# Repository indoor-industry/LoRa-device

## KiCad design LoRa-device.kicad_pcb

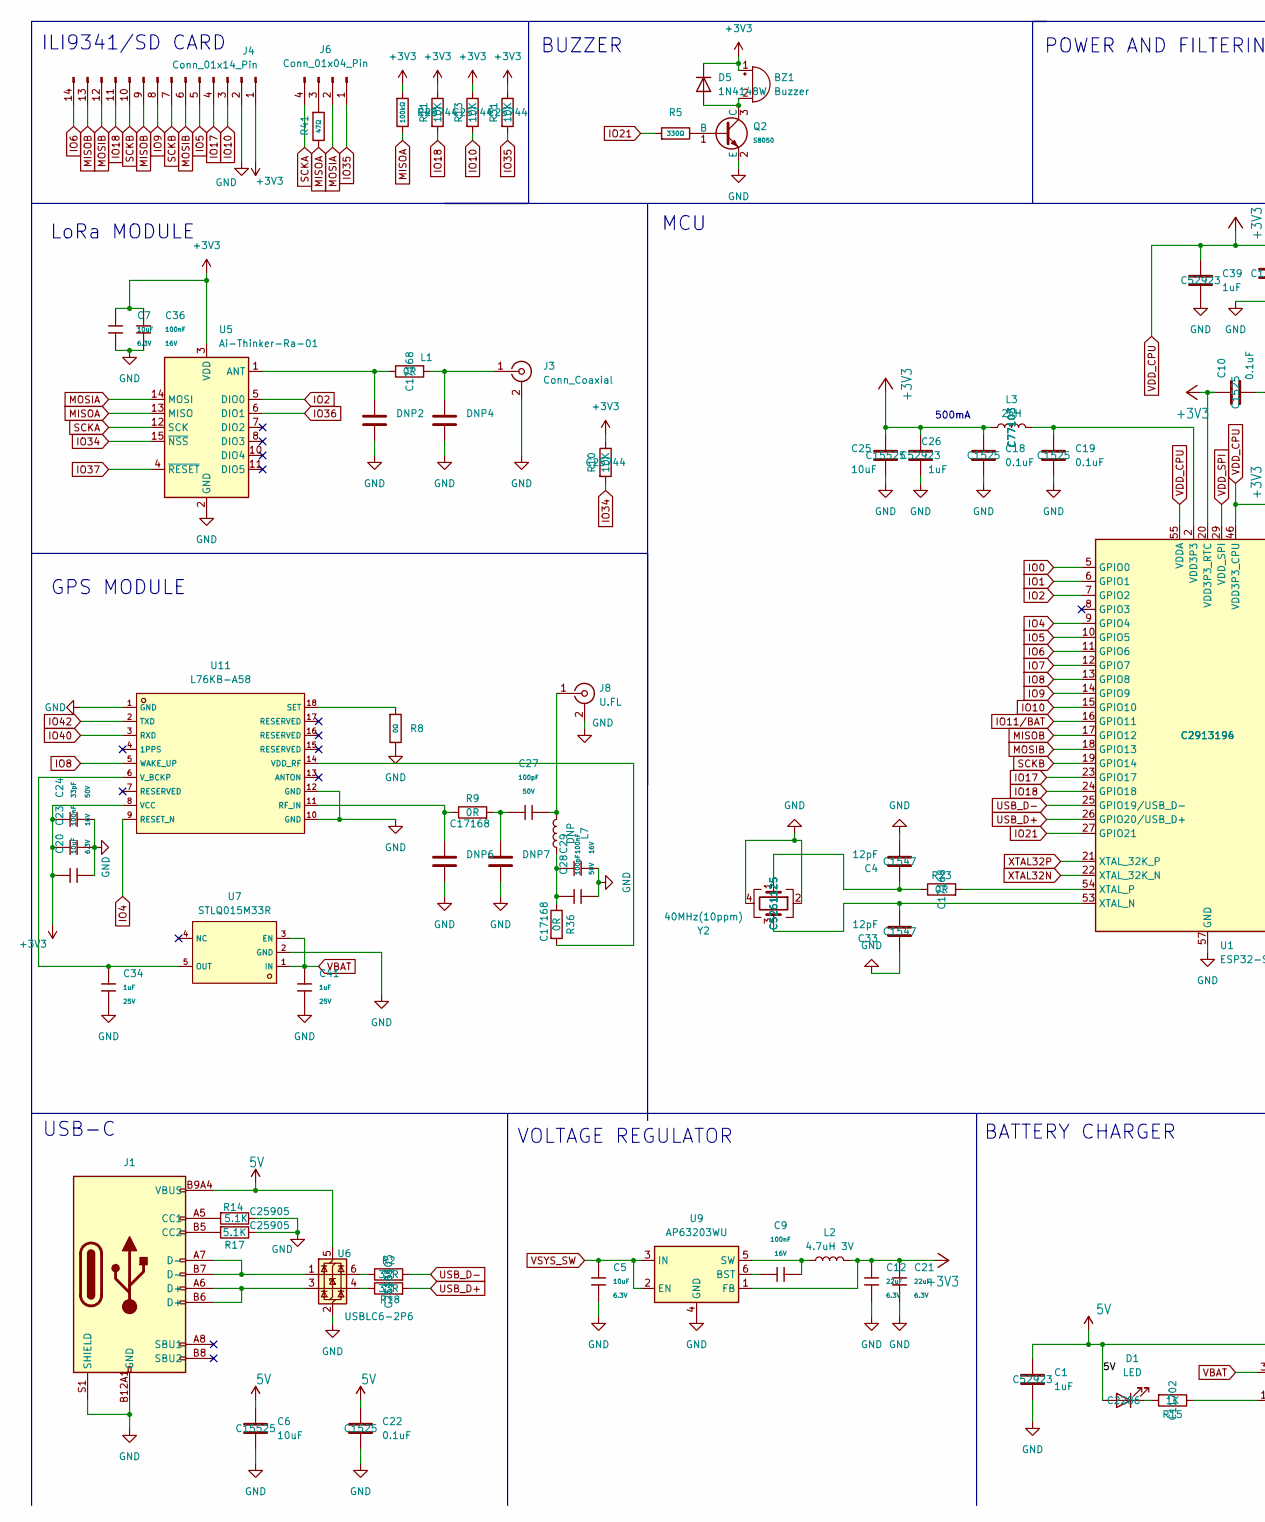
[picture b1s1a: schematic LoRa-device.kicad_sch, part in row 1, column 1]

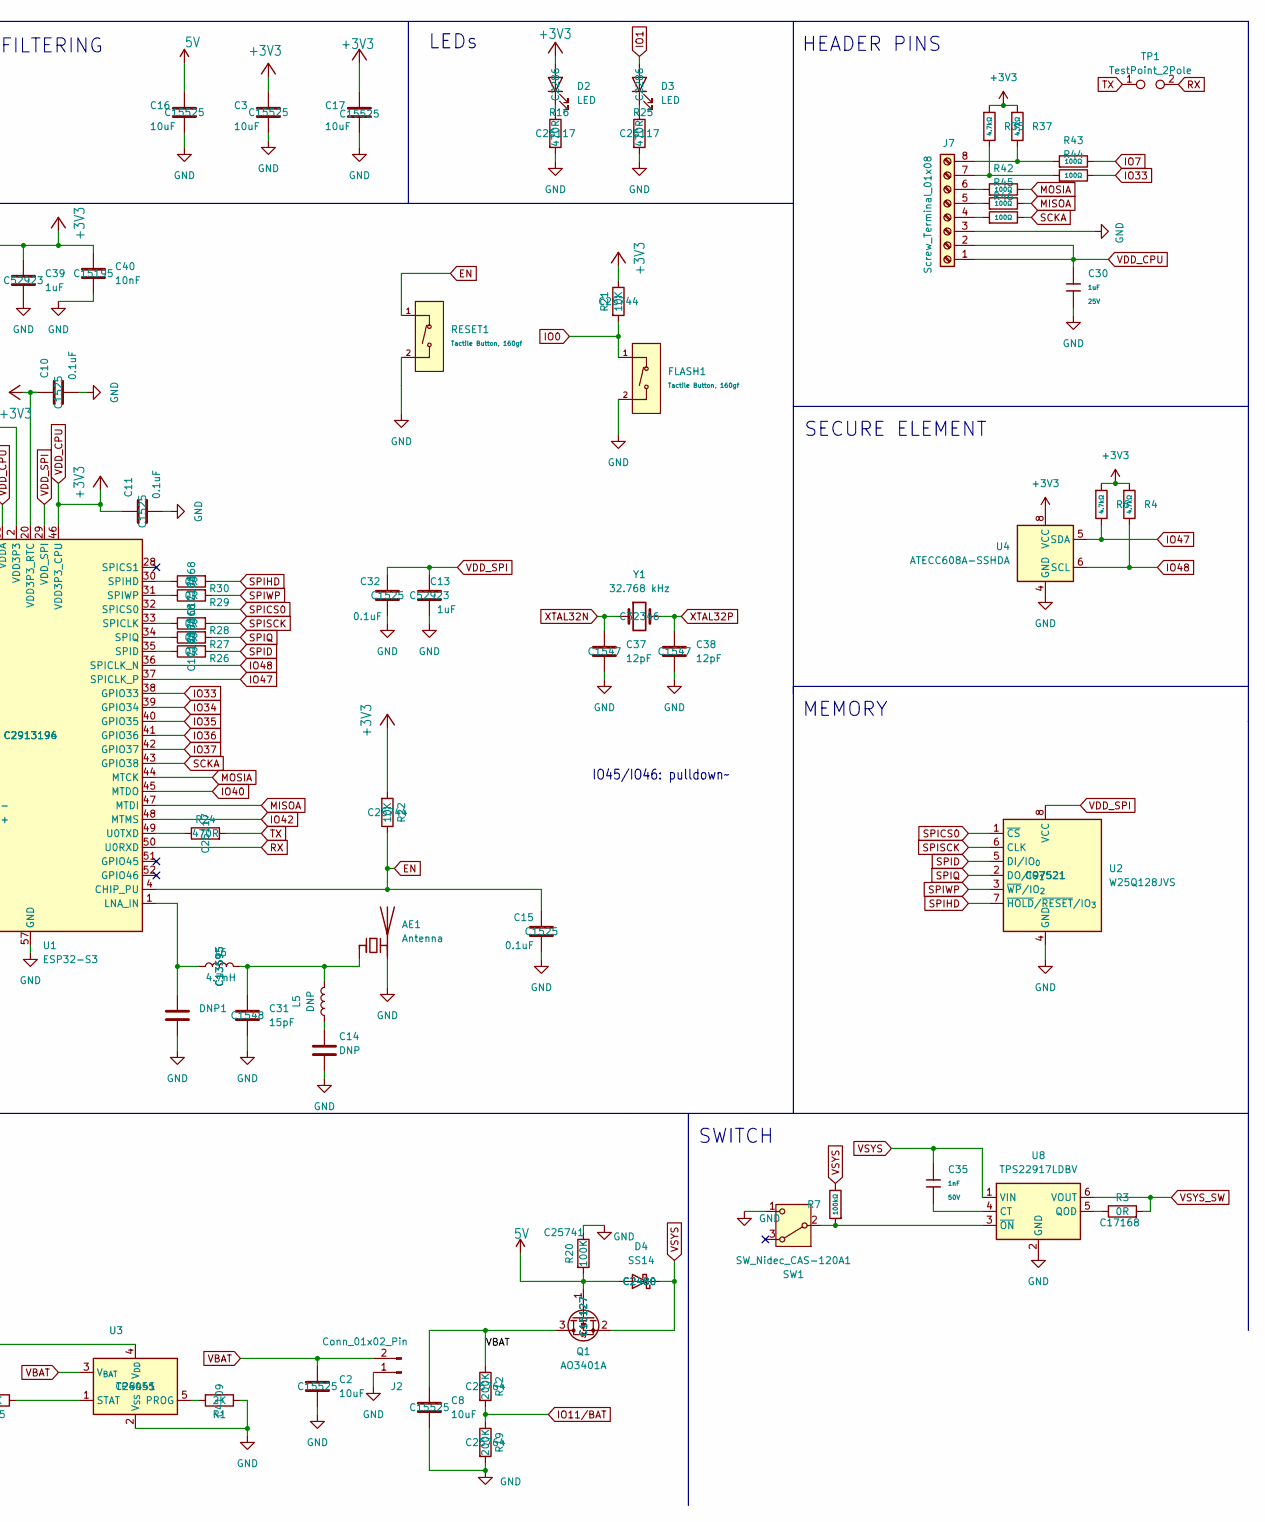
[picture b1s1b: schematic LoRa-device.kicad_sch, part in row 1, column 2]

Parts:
AE1: Antenna; Texas_SWRA117D_2.4GHz_Left
BZ1: Buzzer; MagneticBuzzer_CUI_CMT-8504-100-SMT; MNF PART NUMBER C7437070; LCSC C7437070
C1, C13, C26, C39: 1uF; C_0402_1005Metric; MNF PART NUMBER C52923; LCSC C52923
C2, C3, C6, C8, C16, C17, C25: 10uF; C_0402_1005Metric; MNF PART NUMBER C15525; LCSC C15525
C4, C33, C37, C38: 12pF; C_0402_1005Metric; MNF PART NUMBER C1547; LCSC C1547
C5, C7, C20: 10uF; C_0402; Voltage Rated 6.3V; Tolerance ±20%; Part CL05A106MQ5NUNC; LCSC C15525
C9, C23, C29, C36: 100nF; C_0402; Voltage Rated 16V; Tolerance ±10%; Part CL05B104KO5NNNC; LCSC C1525
C10, C11, C15, C18, C19, C22, C32: 0.1uF; C_0402_1005Metric; MNF PART NUMBER C1525; LCSC C1525
C12, C21: 22uF; C_0603; Voltage Rated 6.3V; Tolerance ±20%; Part CL10A226MQ8NRNC; LCSC C59461
C14: DNP; C_0402_1005Metric
C24: 33pF; C_0402; Voltage Rated 50V; Tolerance ±5%; Part 0402CG330J500NT; LCSC C1562
C27, C28: 100pF; C_0402; Voltage Rated 50V; Tolerance ±5%; Part 0402CG101J500NT; LCSC C1546
C30, C34, C41: 1uF; C_0402; Voltage Rated 25V; Tolerance ±10%; Part CL05A105KA5NQNC; LCSC C52923
C31: 15pF; C_0402_1005Metric; MNF PART NUMBER C1548; LCSC C1548
C35: 1nF; C_0402; Voltage Rated 50V; Tolerance ±10%; Part 0402B102K500NT; LCSC C1523
C40: 10nF; C_0402_1005Metric; MNF PART NUMBER C15195; LCSC C15195
D1, D2, D3: LED; LED_0603_1608Metric; MNF PART NUMBER C2286; LCSC C2286
D4: SS14; LED_0603_1608Metric; MNF PART NUMBER C2480; LCSC C2480
D5: 1N4148W; LED_0603_1608Metric
DNP1, DNP2, DNP4, DNP6, DNP7: C_0402_1005Metric
FLASH1: Tactile Button, 160gf; SW_TS-1088-AR02016; Voltage Rating (Dc) 12V; Part TS-1088-AR02016; LCSC C720477
J1: Connector, USB-TYPE-C-16P; TYPE-C-SMD_HX-TYPE-C-16PIN; LCSC C2927039
J2: Conn_01x02_Pin; PinHeader_1x02_P2.54mm_Vertical
J3: Conn_Coaxial; SMA_Molex_73251-1153_EdgeMount_Horizontal
J4: Conn_01x14_Pin; PinSocket_1x14_P2.54mm_Vertical
J6: Conn_01x04_Pin; PinSocket_1x04_P2.54mm_Vertical
J7: Screw_Terminal_01x08; PhoenixContact_MC_1,5_8-G-3.81_1x08_P3.81mm_Horizontal
J8: U.FL; IPEX-SMD_BWIPX-1-001E; LCSC C5137195
L1: 0R; R_0402_1005Metric; MNF PART NUMBER C17168; LCSC C17168
L2: 4.7uH 3V; L_Sunlord_MWSA0402S; MNF PART NUMBER APH0420T4R7M; LCSC C5349668
L3: 2nH; L_0402_1005Metric; MNF PART NUMBER C77103; LCSC C77103
L5, L7: DNP; L_0402_1005Metric
L6: 4.7nH; L_0402_1005Metric; MNF PART NUMBER C13595; LCSC C13595
Q1: AO3401A; SOT-23; MNF PART NUMBER C15127; LCSC C15127
Q2: S8050; Q_SOT-23; Part S8050; LCSC C364312
R1: 2K; R_0402_1005Metric; MNF PART NUMBER C4109; LCSC C4109
R2, R18: 33R; R_0402_1005Metric; MNF PART NUMBER C25105; LCSC C25105
R3, R9, R23, R26, R27, R28, R29, R30, R36: 0R; R_0402_1005Metric; MNF PART NUMBER C17168; LCSC C17168
R4, R6, R35, R37: 4.7kΩ; R_0402; Overload Voltage (Max) 50V; Tolerance ±1%; Part 0402WGF4701TCE; LCSC C25900
R5: 330Ω; R_0402_1005Metric; Overload Voltage (Max) 50V; Tolerance ±1%; Part 0402WGF3300TCE; LCSC C25104
R7: 100kΩ; R_0402_1005Metric; Overload Voltage (Max) 50V; Tolerance ±1%; Part 0402WGF1003TCE; LCSC C25741
R8: 0Ω; R_0402_1005Metric; Overload Voltage (Max) 50V; Tolerance ±1%; Part 0402WGF0000TCE; LCSC C17168
R10, R11, R13, R21, R22, R31: 10K; R_0402_1005Metric; MNF PART NUMBER C25744; LCSC C25744
R12, R19: 200K; R_0402_1005Metric; MNF PART NUMBER C25764; LCSC C25764
R14, R17: 5.1K; R_0402_1005Metric; MNF PART NUMBER C25905; LCSC C25905
R15: 1K; R_0402_1005Metric; MNF PART NUMBER C11702; LCSC C11702
R16, R24, R25: 470R; R_0402_1005Metric; MNF PART NUMBER C25117; LCSC C25117
R20: 100K; R_0402_1005Metric; MNF PART NUMBER C25741; LCSC C25741
R40: 100kΩ; R_0402; Overload Voltage (Max) 50V; Tolerance ±1%; Part 0402WGF1003TCE; LCSC C25741
R41: 47Ω; R_0402; Overload Voltage (Max) 50V; Tolerance ±1%; Part 0402WGF470JTCE; LCSC C25118
R42, R43, R44, R45, R46: 100Ω; R_0402; Overload Voltage (Max) 50V; Tolerance ±1%; Part 0402WGF1000TCE; LCSC C25076
RESET1: Tactile Button, 160gf; SW_TS-1088-AR02016; Voltage Rating (Dc) 12V; Part TS-1088-AR02016; LCSC C720477
SW1: SW_Nidec_CAS-120A1; PinHeader_1x02_P2.54mm_Vertical
TP1: TestPoint_2Pole; TestPoint_2Pads_Pitch2.54mm_Drill0.8mm
U1: ESP32-S3; QFN-56-1EP_7x7mm_P0.4mm_EP4x4mm; MNF PART NUMBER C2913196; LCSC C2913194
U2: W25Q128JVS; SOIC-8_5.3x5.3mm_P1.27mm; MNF PART NUMBER C97521; LCSC C97521
U3: TP4055; SOT-23-5; MNF PART NUMBER TP4055; LCSC C28441
U4: ATECC608A-SSHDA; SOIC-8_3.9x4.9mm_P1.27mm
U5: Ai-Thinker-Ra-01; Ai-Thinker-Ra-01-LoRa; MNF PART NUMBER C503593; LCSC C503593
U6: USBLC6-2P6; SOT-666
U7: STLQ015M33R; SOT-23-5_L3.0-W1.7-P0.95-LS2.8-BR; LCSC C136154
U8: TPS22917LDBV; SOT-23-6; MNF PART NUMBER C3235537; LCSC C3235537
U9: AP63203WU; TSOT-23-6; MNF PART NUMBER AP63203WU-7; LCSC C780769
U11: L76KB-A58; GPSM-SMD_18P-L10.1-W9.7-P1.10; LCSC C2916234
Y1: 32.768 kHz; Crystal_SMD_3215-2Pin_3.2x1.5mm; MNF PART NUMBER C32346; LCSC C32346
Y2: 40MHz(10ppm); Crystal_SMD_2520-4Pin_2.5x2.0mm; MNF PART NUMBER C5261125; LCSC C5261125

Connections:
5V: C1.1, C6.1, C16.1, C22.1, D1.2 (A), D4.2 (A), J1.A9B4 (VBUS), J1.B9A4 (VBUS), Q1.1 (G), R20.2, U3.4 (V_{DD}), U6.5 (VBUS)
EN: C15.1, R22.1, RESET1.1 (A), U1.4 (CHIP_PU)
GND: AE1.2 (PCB_Trace), C1.2, C2.2, C3.2, C4.2, C5.1, C6.2, C7.2, C8.2, C10.2, C11.2, C12.2, C13.2, C14.2, C15.2, C16.2, C17.2, C18.2, C19.2, C20.2, C21.2, C22.2, C23.2, C24.2, C25.2, C26.2, C28.2, C29.2, C30.2, C31.2, C32.2, C33.1, C34.2, C36.2, C37.2, C38.2, C39.2, C40.2, C41.2, DNP1.2, DNP2.2, DNP4.2, DNP6.2, DNP7.2, FLASH1.2 (B), J1.A12B1 (GND), J1.B12A1 (GND), J1.S1 (SHIELD), J2.1, J3.2 (Ext), J4.2, J7.3, J8.2 (Ext), Q2.2 (E), R1.1, R8.2, R14.1, R16.2, R17.1, R19.2, R20.1, R25.2, RESET1.2 (B), SW1.1 (C), U1.57 (GND), U2.4 (GND), U3.2 (V_{SS}), U4.4 (GND), U5.2 (GND), U5.9 (GND), U5.16 (GND), U6.2 (GND), U7.2 (GND), U8.2 (GND), U9.4 (GND), U11.1 (GND), U11.10 (GND), U11.12 (GND), Y2.2, Y2.4
IO0: FLASH1.1 (A), R21.2, U1.5 (GPIO0)
IO1: D3.2 (A), U1.6 (GPIO1)
IO2: U1.7 (GPIO2), U5.5 (DIO0)
IO4: U1.9 (GPIO4), U11.9 (RESET_N)
IO5: J4.5, U1.10 (GPIO5)
IO6: J4.14, U1.11 (GPIO6)
IO7: R43.2, U1.12 (GPIO7)
IO8: U1.13 (GPIO8), U11.5 (WAKE_UP)
IO9: J4.8, U1.14 (GPIO9)
IO10: J4.3, R13.2, U1.15 (GPIO10)
IO11/BAT: R12.2, R19.1, U1.16 (GPIO11)
IO17: J4.4, U1.23 (GPIO17)
IO18: J4.11, R11.2, U1.24 (GPIO18)
IO21: R5.1, U1.27 (GPIO21)
IO33: R44.2, U1.38 (GPIO33)
IO34: R10.2, U1.39 (GPIO34), U5.15 (~NSS)
IO35: J6.1, R31.2, U1.40 (GPIO35)
IO36: U1.41 (GPIO36), U5.6 (DIO1)
IO37: U1.42 (GPIO37), U5.4 (~RESET)
IO40: U1.45 (MTDO), U11.3 (RXD)
IO42: U1.48 (MTMS), U11.2 (TXD)
IO47: R6.2, U1.37 (SPICLK_P), U4.5 (SDA)
IO48: R4.2, U1.36 (SPICLK_N), U4.6 (SCL)
MISOA: R40.2, R41.2, R45.2, U1.47 (MTDI), U5.13 (MISO)
MISOB: J4.9, J4.13, U1.17 (GPIO12)
MOSIA: J6.2, R42.2, U1.44 (MTCK), U5.14 (MOSI)
MOSIB: J4.6, J4.12, U1.18 (GPIO13)
unnamed: AE1.1 (FEED), C31.1, L5.2, L6.2
unnamed: BZ1.2 (-), D5.2 (A), Q2.3 (C)
unnamed: C4.1, R23.1, Y2.1
unnamed: C14.1, L5.1
unnamed: C19.1, L3.2, U1.2 (VDD3P3), U1.3 (VDD3P3)
unnamed: C27.1, DNP7.1, R9.2
unnamed: C28.1, C29.1, L7.1, R36.1
unnamed: D1.1 (K), R15.2
unnamed: D2.1 (K), R16.1
unnamed: D3.1 (K), R25.1
unnamed: J1.A5 (CC1), R14.2
unnamed: J1.B5 (CC2), R17.2
unnamed: J1.A6 (D+), J1.B6 (D+), U6.3 (I/O2)
unnamed: J1.A7 (D-), J1.B7 (D-), U6.1 (I/O1)
unnamed: DNP4.1, J3.1 (In), L1.2
unnamed: J6.3, R41.1
unnamed: J7.4, R46.1
unnamed: J7.5, R45.1
unnamed: J7.6, R42.1
unnamed: J7.7, R35.2, R44.1
unnamed: J7.8, R37.2, R43.1
unnamed: C27.2, J8.1 (In), L7.2
unnamed: Q2.1 (B), R5.2
unnamed: R2.1, U6.6 (I/O1)
unnamed: R18.1, U6.4 (I/O2)
unnamed: R7.1, SW1.2 (B), U8.3 (~ON)
unnamed: DNP1.1, L6.1, U1.1 (LNA_IN)
unnamed: R28.1, U1.33 (SPICLK)
unnamed: R26.1, U1.35 (SPID)
unnamed: R30.1, U1.30 (SPIHD)
unnamed: R27.1, U1.34 (SPIQ)
unnamed: R29.1, U1.31 (SPIWP)
unnamed: R24.1, U1.49 (U0TXD)
unnamed: C33.2, U1.53 (XTAL_N), Y2.3
unnamed: R23.2, U1.54 (XTAL_P)
unnamed: R1.2, U3.5 (PROG)
unnamed: R15.1, U3.1 (STAT)
unnamed: DNP2.1, L1.1, U5.1 (ANT)
unnamed: C35.2, U8.4 (CT)
unnamed: R3.1, U8.5 (QOD)
unnamed: C9.1, U9.6 (BST)
unnamed: C9.2, L2.1, U9.5 (SW)
unnamed: DNP6.1, R9.1, U11.11 (RF_IN)
unnamed: R8.1, U11.18 (SET)
unnamed: R36.2, U11.14 (VDD_RF)
unnamed: C34.1, U7.5 (OUT), U11.6 (V_BCKP)
RX: TP1.2, U1.50 (U0RXD)
SCKA: J6.4, R46.2, U1.43 (GPIO38), U5.12 (SCK)
SCKB: J4.7, J4.10, U1.19 (GPIO14)
SPICS0: U1.32 (SPICS0), U2.1 (~CS)
SPID: R26.2, U2.5 (DI/IO_{0})
SPIHD: R30.2, U2.7 (~HOLD/~RESET/IO_{3})
SPIQ: R27.2, U2.2 (DO/IO_{1})
SPISCK: R28.2, U2.6 (CLK)
SPIWP: R29.2, U2.3 (~WP/IO_{2})
TX: R24.2, TP1.1
USB_D+: R18.2, U1.26 (GPIO20/USB_D+)
USB_D-: R2.2, U1.25 (GPIO19/USB_D-)
VBAT: C2.1, C8.1, C41.1, J2.2, Q1.3 (D), R12.1, U3.3 (V_{BAT}), U7.1 (IN), U7.3 (EN)
VDD_CPU: BZ1.1 (+), C3.1, C7.1, C10.1, C11.1, C12.1, C17.1, C18.1, C20.1, C21.1, C23.1, C24.1, C25.1, C26.1, C30.1, C36.1, C39.1, C40.1, D2.2 (A), D5.1 (K), J4.1, J7.1, J7.2, L2.2, L3.1, R4.1, R6.1, R10.1, R11.1, R13.1, R21.1, R22.2, R31.1, R35.1, R37.1, R40.1, U1.20 (VDD3P3_RTC), U1.46 (VDD3P3_CPU), U1.55 (VDDA), U1.56 (VDDA), U4.8 (VCC), U5.3 (VDD), U9.1 (FB), U11.8 (VCC)
VDD_SPI: C13.1, C32.1, U1.29 (VDD_SPI), U2.8 (VCC)
VSYS: C35.1, D4.1 (K), Q1.2 (S), R7.2, U8.1 (VIN)
VSYS_SW: C5.2, R3.2, U8.6 (VOUT), U9.2 (EN), U9.3 (IN)
XTAL32N: C37.1, U1.22 (XTAL_32K_N), Y1.1
XTAL32P: C38.1, U1.21 (XTAL_32K_P), Y1.2

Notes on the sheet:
BATTERY CHARGER
VOLTAGE REGULATOR
BUZZER
LoRa MODULE
500mA
LEDs
MCU
HEADER PINS
MEMORY
GPS MODULE
ILI9341/SD CARD
SWITCH
POWER AND FILTERING
IO45/IO46: pulldown~~{}
USB-C
SECURE ELEMENT

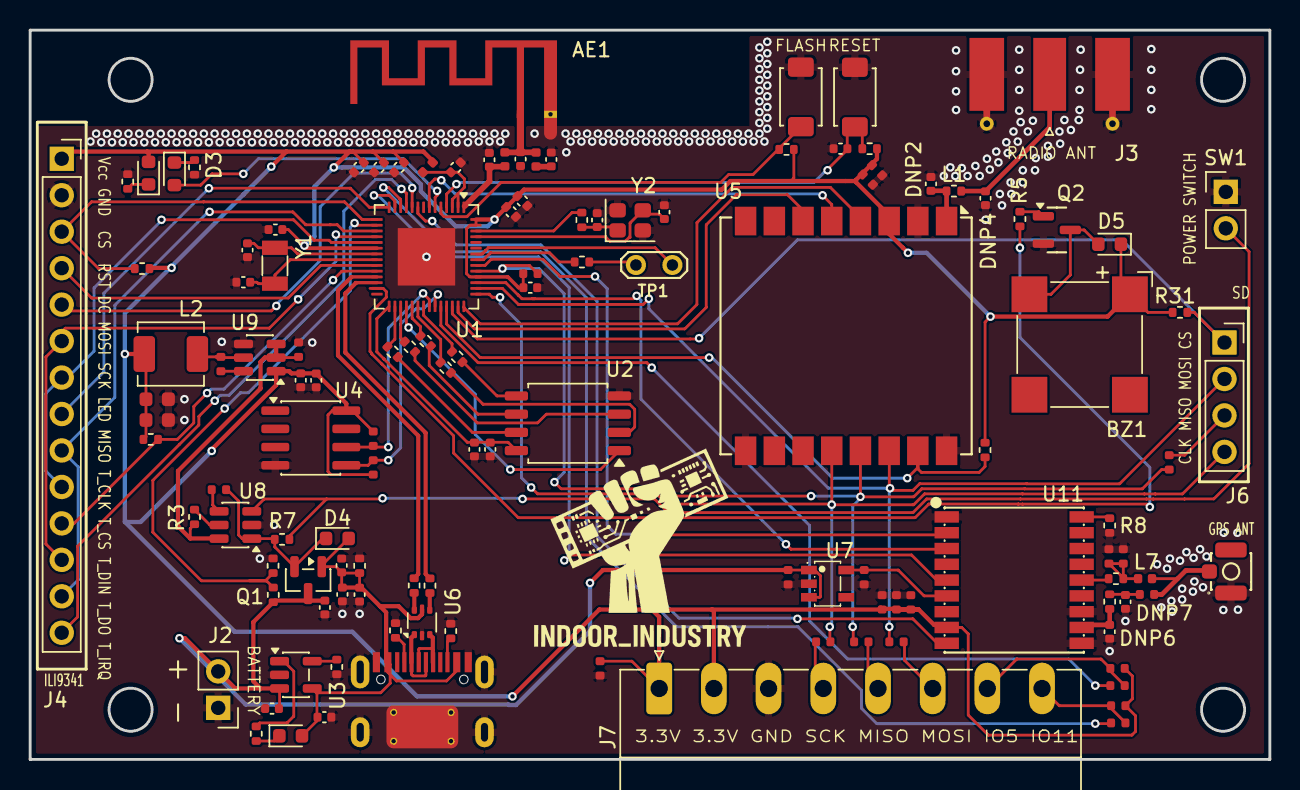
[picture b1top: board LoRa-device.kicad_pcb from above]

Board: 4 copper layers, 86.4 x 50.8 mm, 125 parts (0 on the bottom side), 95 nets.

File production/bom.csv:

Designator,Footprint,Quantity,Value,LCSC Part #
AE1,Texas_SWRA117D_2.4GHz_Left,1,Antenna,
BZ1,MagneticBuzzer_CUI_CMT-8504-100-SMT,1,Buzzer,C7437070
"C1, C13, C26, C39",0402,4,1uF,C52923
"C10, C11, C15, C18, C19, C22, C32",0402,7,0.1uF,C1525
"C12, C21",C_0603,2,22uF,C59461
"C14, L5, L7",0402,3,DNP,
"C16, C17, C2, C25, C3, C6, C8",0402,7,10uF,C15525
"C20, C5, C7",C_0402,3,10uF,C15525
"C23, C29, C36, C9",C_0402,4,100nF,C1525
C24,C_0402,1,33pF,C1562
"C27, C28",C_0402,2,100pF,C1546
"C30, C34, C41",C_0402,3,1uF,C52923
C31,0402,1,15pF,C1548
"C33, C37, C38, C4",0402,4,12pF,C1547
C35,C_0402,1,1nF,C1523
C40,0402,1,10nF,C15195
"D1, D2, D3",0603,3,LED,C2286
D4,0603,1,SS14,C2480
D5,0603,1,1N4148W,
"DNP1, DNP2, DNP4, DNP6, DNP7",0402,5,~,
"FLASH1, RESET1",SW_TS-1088-AR02016,2,"Tactile Button, 160gf",C720477
J1,TYPE-C-SMD_HX-TYPE-C-16PIN,1,"Connector, USB-TYPE-C-16P",C2927039
J2,PinHeader_1x02_P2.54mm_Vertical,1,Conn_01x02_Pin,
J3,SMA_Molex_73251-1153_EdgeMount_Horizontal,1,Conn_Coaxial,
J4,PinSocket_1x14_P2.54mm_Vertical,1,Conn_01x14_Pin,
J6,PinSocket_1x04_P2.54mm_Vertical,1,Conn_01x04_Pin,
J7,"PhoenixContact_MC_1,5_8-G-3.81_1x08_P3.81mm_Horizontal",1,Screw_Terminal_01x08,
J8,IPEX-SMD_BWIPX-1-001E,1,U.FL,C5137195
"L1, R23, R26, R27, R28, R29, R3, R30, R36, R9",0402,10,0R,C17168
L2,L_Sunlord_MWSA0402S,1,4.7uH 3V,C5349668
L3,0402,1,2nH,C77103
L6,0402,1,4.7nH,C13595
Q1,SOT-23,1,AO3401A,C15127
Q2,Q_SOT-23,1,S8050,C364312
R1,0402,1,2K,C4109
"R10, R11, R13, R21, R22, R31",0402,6,10K,C25744
"R12, R19",0402,2,200K,C25764
"R14, R17",0402,2,5.1K,C25905
R15,0402,1,1K,C11702
"R16, R24, R25",0402,3,470R,C25117
"R18, R2",0402,2,33R,C25105
R20,0402,1,100K,C25741
"R35, R37, R4, R6",R_0402,4,4.7kΩ,C25900
R40,R_0402,1,100kΩ,C25741
R41,R_0402,1,47Ω,C25118
"R42, R43, R44, R45, R46",R_0402,5,100Ω,C25076
R5,0402,1,330Ω,C25104
R7,0402,1,100kΩ,C25741
R8,0402,1,0Ω,C17168
SW1,PinHeader_1x02_P2.54mm_Vertical,1,SW_Nidec_CAS-120A1,
TP1,TestPoint_2Pads_Pitch2.54mm_Drill0.8mm,1,TestPoint_2Pole,
U1,QFN-56-1EP_7x7mm_P0.4mm_EP4x4mm,1,ESP32-S3,C2913194
U11,GPSM-SMD_18P-L10.1-W9.7-P1.10,1,L76KB-A58,C2916234
U2,SOIC-8_5.3x5.3mm_P1.27mm,1,W25Q128JVS,C97521
U3,SOT-23-5,1,TP4055,C28441
U4,SOIC-8_3.9x4.9mm_P1.27mm,1,ATECC608A-SSHDA,
U5,Ai-Thinker-Ra-01-LoRa,1,Ai-Thinker-Ra-01,C503593
U6,SOT-666,1,USBLC6-2P6,
U7,SOT-23-5_L3.0-W1.7-P0.95-LS2.8-BR,1,STLQ015M33R,C136154
U8,SOT-23-6,1,TPS22917LDBV,C3235537
U9,TSOT-23-6,1,AP63203WU,C780769
Y1,Crystal_SMD_3215-2Pin_3.2x1.5mm,1,32.768 kHz,C32346
Y2,Crystal_SMD_2520-4Pin_2.5x2.0mm,1,40MHz(10ppm),C5261125

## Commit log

2026-01-26 New layout, routing in progress
2026-01-27 First routing
2026-01-28 Completed routing
2026-02-03 Major rerouting and ESD protection for USB port
2026-02-04 Routing complete, case work begins
2026-02-05 Case work begun, 4 layers board
2026-02-07 Further refinements
2026-02-08 Power supply overhaul
2026-02-09 Added secure component
2026-02-10 3d model, case space for battery.
2026-02-11 External header protection, clean routing
2026-02-13 L76K V_BCKP added
